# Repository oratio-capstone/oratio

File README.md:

# Oratio

Oratio is an off-grid, mesh-based emergency telecommunications system.
Computer engineering capstone by Adam Dia, Yadah Ngolo, Fayza Oyarekhua, Mohamed Boustta and Omon Okondo.

The system comprises of wearable nodes participating in a wireless mesh, a Raspberry Pi hosting a UDP server for forwarding and a dashboard.

## Organization

- `fw` contains all of our firmware
- `hw` contains PCB schematics and enclosure
- `sw` contains the UDP server and dashboard

## Versions

| Component | Version |
| --- | --- |
| PlatformIO Core | 6.1.19 |
| Pioarduino platform | 54.03.21-2 |
| ESP-IDF | 5.4.2 |
| ESP-Mesh-Lite | 1.0.2 |
| IoT-Bridge | 1.0.1 |

## Local firmware builds

Use PlatformIO Core 6.1.19 to match CI. From the repository root in PowerShell:

```powershell
python -m venv fw/.venv-pio
& fw/.venv-pio/Scripts/python.exe -m pip install platformio==6.1.19
& fw/.venv-pio/Scripts/Activate.ps1
pio --version
cd fw
```

If the virtual environment already exists, reuse it and install the pinned version
there. PlatformIO downloads its platform/tool packages automatically into the normal
user .platformio directory. That directory does not select the pio executable version.
Generated sdkconfig files and the virtual environment are local, ignored build state.

Build the S3 root and node firmware:

```powershell
pio run -e root -e node
```

Build and link a test suite without uploading or running it:

```powershell
pio test -e root_test -f test_155_protocol --without-uploading --without-testing
```

The same build-only command supports test_102_mesh, test_106_udp,
test_109_heartbeat, and test_113_relay. Hardware tests require the appropriate board,
serial port, network settings, and gateway setup. Successful build-only checks are
not hardware test passes.

### Board-specific flash defaults

Shared network settings live in fw/sdkconfig.defaults. ESP-IDF automatically adds
fw/sdkconfig.defaults.esp32s3 for the S3: 8 MB flash and the console on the S3's
native USB port (plug into the USB port, not the UART one, to see logs). These small defaults files
belong in version control; generated per-environment sdkconfig files do not.
Existing generated configurations retain their saved settings, so check/regenerate
local configuration when changing board assumptions; preserve any local credentials.

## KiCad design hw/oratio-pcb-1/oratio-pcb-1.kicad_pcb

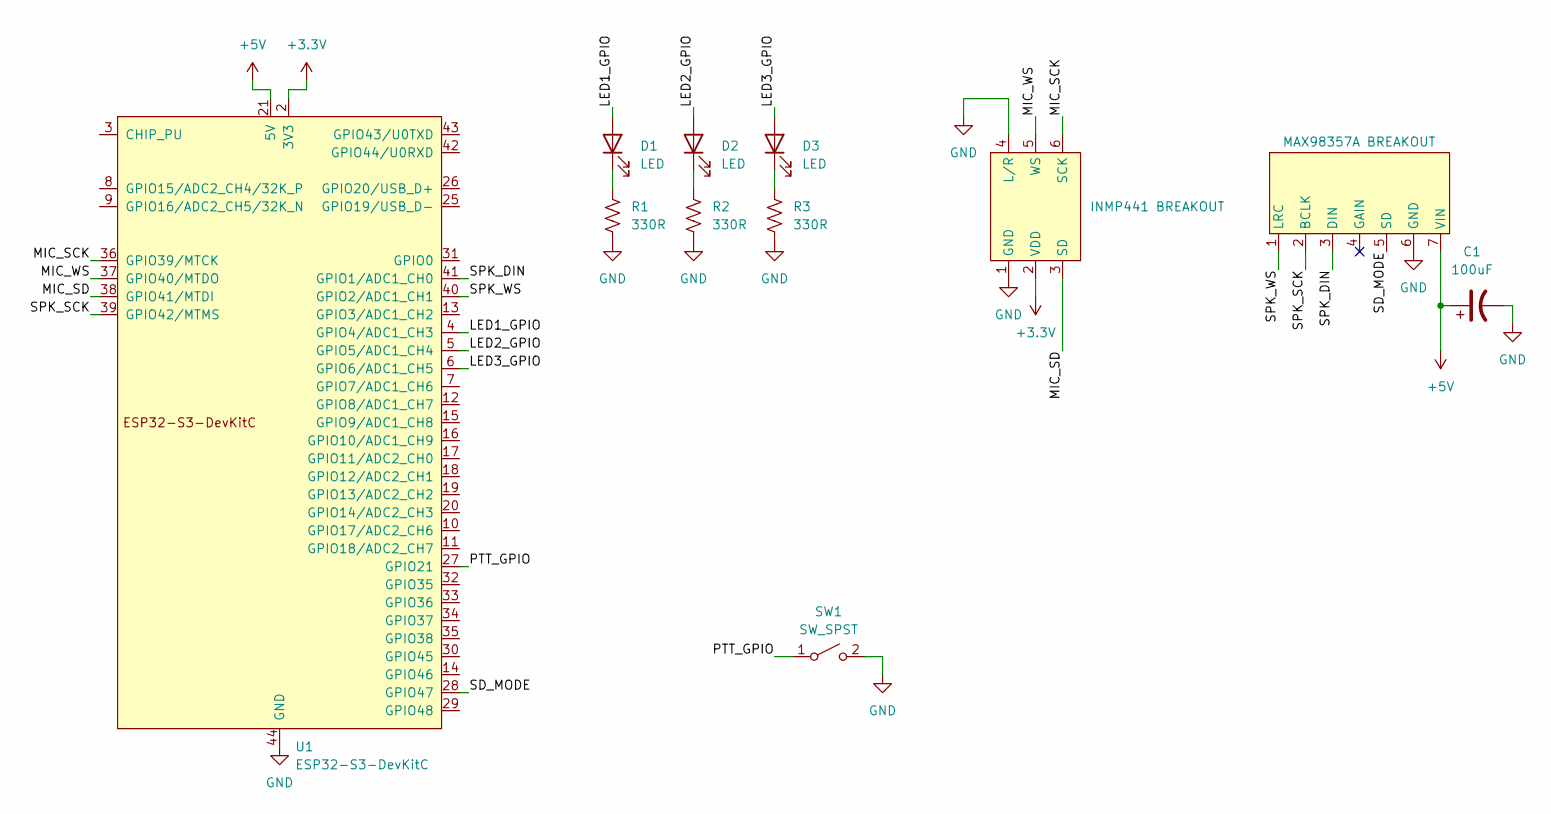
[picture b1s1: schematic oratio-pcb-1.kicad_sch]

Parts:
C1: 100uF; CP_Radial_D5.0mm_P2.00mm
D1, D2, D3: LED; LED_D3.0mm
R1, R2, R3: 330R; R_Axial_DIN0207_L6.3mm_D2.5mm_P7.62mm_Horizontal
SW1: SW_SPST; SW_PUSH_6mm_H5mm
U1: ESP32-S3-DevKitC
U2: INMP441 BREAKOUT; INMP441_Breakout
U3: MAX98357A BREAKOUT; MAX98357A_Breakout

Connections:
+3.3V: U1.1 (3V3), U1.2 (3V3), U2.2 (VDD)
+5V: C1.1, U1.21 (5V), U3.7 (VIN)
/LED1_GPIO: D1.2 (A), U1.4 (GPIO4/ADC1_CH3)
/LED2_GPIO: D2.2 (A), U1.5 (GPIO5/ADC1_CH4)
/LED3_GPIO: D3.2 (A), U1.6 (GPIO6/ADC1_CH5)
/MIC_SCK: U1.36 (GPIO39/MTCK), U2.6 (SCK)
/MIC_SD: U1.38 (GPIO41/MTDI), U2.3 (SD)
/MIC_WS: U1.37 (GPIO40/MTDO), U2.5 (WS)
/PTT_GPIO: SW1.1 (A), U1.27 (GPIO21)
/SD_MODE: U1.28 (GPIO47), U3.5 (SD)
/SPK_DIN: U1.41 (GPIO1/ADC1_CH0), U3.3 (DIN)
/SPK_SCK: U1.39 (GPIO42/MTMS), U3.2 (BCLK)
/SPK_WS: U1.40 (GPIO2/ADC1_CH1), U3.1 (LRC)
GND: C1.2, R1.2, R2.2, R3.2, SW1.2 (B), U1.22 (GND), U1.23 (GND), U1.24 (GND), U1.44 (GND), U2.1 (GND), U2.4 (L/R), U3.6 (GND)
unnamed: D1.1 (K), R1.1
unnamed: D2.1 (K), R2.1
unnamed: D3.1 (K), R3.1

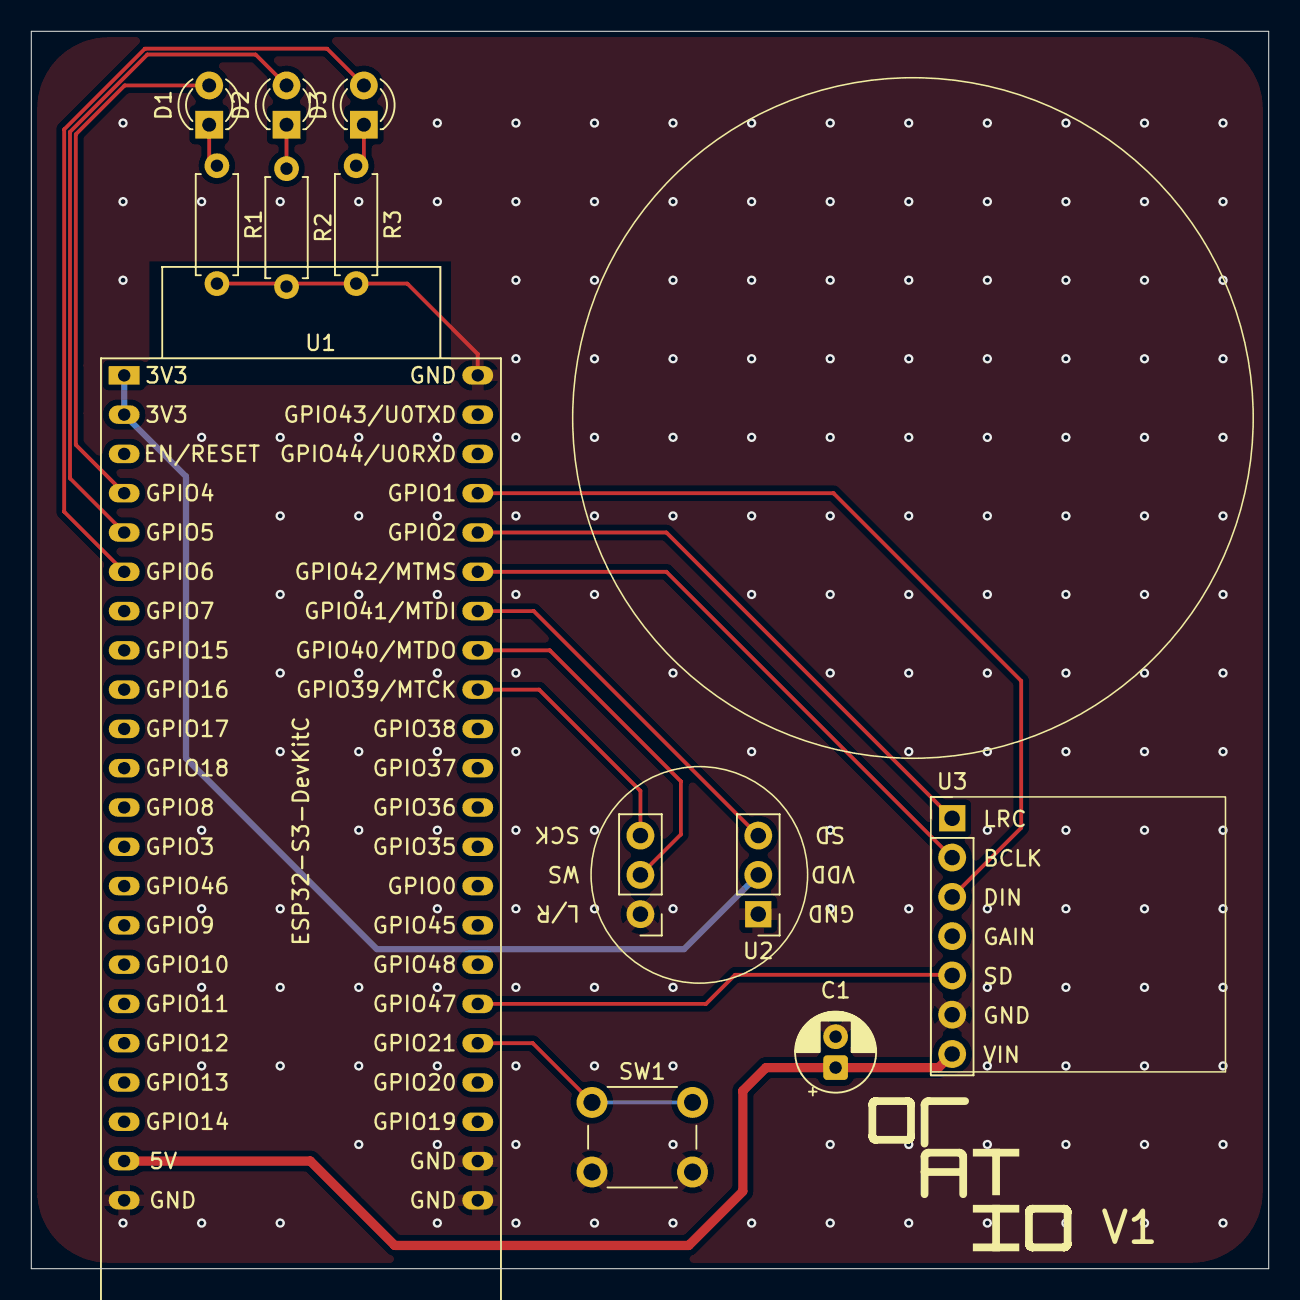
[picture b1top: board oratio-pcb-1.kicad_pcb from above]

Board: 2 copper layers, 80.0 x 80.0 mm, 11 parts (0 on the bottom side), 17 nets.
